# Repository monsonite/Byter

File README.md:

# Byter
A basic 8-bit, bit serial CPU in 74HCxx Logic.

## PART 1. Getting Started On The Basics.

Bit Serial Arithmetic is sufficiently obscure to most - you have to start with the basics.

When I started this journey during the first COVID lockdown - it took many iterations to get the basic hardware to work using the "Digital" simulator.

First you need a full adder, then extend it to a complete ALU.
 
You add your Accumulator and B shift registers and make a simple adder -subtractor.

You need the Carry Flipflop and the Carry injection and suppression logic.

Finally you need a a clock sequencer to make it all work correctly.

This repo - will takes you through the basics:

The following is NOT a full CPU, it is just an ALU testbed to ensure that the serial arithmetic process is working correctly.

### 1. INSTRUCTION DECODER

We start with the instruction Decoder.  U1 (74HC138) decodes the 3-bit instruction in IR6:4 into one of the 8 fundamental instruction groups:

LOAD

AND

OR

XOR

ADD

SUB

STORE

JUMP

The didode matrix and U2 (octal inverter 74HC540) converts these instructions into control signals that will control the ALU and carry logic.

The Instruction Decoder is entirely combinational logic, so could be reduced to basic gates or even coded into a ROM.

### 2. ALU

The ALU is entirely combinational logic made entirely from basic gates so could be coded into a ROM.

It has 12 inputs, and 5 outputs:

Ain   The bitstream from the Accumulator Shift Register

Bin   The bitstream from the B Shift Register

Cin   Any Carry generated from the previous bit-sum

InvA  Invert the A input for B-A subtraction operations

InvB  Invert the B input for A-B subtraction operations

Mode  Suppress Carry propagation for logical operations

SetC (T1)  Set the Carry on Timing Pulse T1

Sub   Asserted to indicate when a subtraction is performed

LDA (T0) Timing Pulse T0 initiates loading of the Accumulator

CLA  Clear Accumulator first, if a LOAD instruction is being performed

I0 Instruction input 0 - selects whether ALU output is the SUM function

I0 Instruction input  -  selects whether ALU output is the CARRY function

I1:I0   00    ZERO 

I1:I0   01    XOR

I1:I0   10    AND 

I1:I0   11    OR

OUTPUTS:

Fout  - The SUM Output of the ALU

Cout  - The CARRY output of the ALU

/CSET - Preset the Carry Flipflop

/CRES - Pre-clear the Carry Flipflop

/CLRACC - Clear the Accumulator

Details:

One quand 2-input XOR and three quad 2-input NANDs.  U10:U13.

U10, 11 and 12 make up the ALU, and U13 deals with the Carry suppress and injection logic.

U10 and U11 form a full adder with the means to invert either of the two inputs A and B.

U12 creates a 2 input multiplexer that chooses either the AND (CARRY) term or the XOR (SUM) term from the full adder.

U13 provides a means to inject a carry when it is needed and suppress the carry chain during logical operations.

### 3. The Clock Sequencer.

The clock sequencer is based around a 4-bit counter (74HC161) U8. When clocked, this counter will count from 0 to 15 and on the $0F count produces the RCO (Ripple Carry Out) signal. RCO is captured by one half of the dual flipflop U9 and is used to produce true and complementary timing pulses RUN and T0.

U7 (74HC00) is a clock gating circuit.  Two of the NAND gates are configured as a SR latch. RES goes low, and is used to reset the latch. This makes the output RST high and allows the clock signal CLK to pass to the counter U8. when RST goes high the counter is taken out of reset and begins to count upwards from 0 to 15.

RST is effectively a clock gating signal. When high it allows a burst of clocks to be sent to the various shift registers - thus synchronising their operations. The inverted form of RST is available from the output of the lower NAND gate. This can be used as a /CE or /SS (slave select) signal for enabling SPI peripherals.

Carry Flipflop.

The other half of dual flipflop U9 is the "Carry Flipflop".  If a positive carry is generated during a bit-sum, it will be stored in U9B and presented to the Carry In (Cin) input of the ALU on the next clock cycle. The set and reset inputs of the flipflop are used to set or clear the carry, as required by the instruction being performed. For example a subtraction requires the carry to be set first at the start of the calculation but bitwise boolean logical operations require the carry to be suppressed for the duration of the operation so that it does not propagate between the bits and corrupt the operation.

### 4. Registers.

I show 3 registers, The Accumulator AC, The B-Register and an Output Register. The output register just follows the Accumulator - but just latches its output result at the end of the machine cycle. All are 8-bits and they are co-ordinated by the timing pulses and the gated clock stream GCLK.

In the next part, I will show how other ICs can be used to replace U2, U10, 11, 12, 13 thus reducing the package count.  

The Instruction decoding logic can be simplified and the Carry Suppress logic moved to the Carry Flipflop, rather than using additional NAND gates.

The clock sequencer counter may be set to generate different numbers of pulses in the clock burst. These van be used to control the Accumulator to provide left and right shift operations and also a nybble swap operation between the upper 4-bits and the lower 4-bits.

## Part 2. Reducing package count - or getting more bang for your buck!

All combinational logic may ultimately be reduced to a ROM or other programmable logic such as PAL, GAL or FPGA.  These are all "blackbox" solutions, and not easy to follow as a newcomer to bit serial architechtures.

However, by carefully choosing devices that are more specialised, and contain more logic than basic 2-input gates, fairly large savings may be made in package count, and in some cases, these devices offer additional functionality, which previously would have required further packages.

I am initially going to focus on the Instruction Decoder and ALU. Between these sub-circuits, they use 6 packages, 1x 20 pin, 1x 16 pin and 4x 14-pin - plus an array of 15 diodes, which on a pcb would take up the same space as a pair of 14 pin DILs. 

We will keep U1, the 74HC138, as this is a very convenient way to perform the first stage of instruction decoding. We will eliminate the octal inverter and the diode matrix and its accompanying pull-up resistors.

We will minimise the rest of the decode logic finding a better overall solution for U12 and U13.

At the same time we will start to turn this manual adder/subtractor into a working CPU, allowing it to run stored programs from parallel memory.

This will require a Program Counter and additional circuitry, some of which will be absorbed into the enhanced ALU design.

A Better ALU Solution.

At this stage I would like to introduce the 74HC283 - it is a 4-bit parallel adder, with fast carry logic. Here you might say, but we only need a 1-bit full adder - a valid point. But the 74HC283 can provide an independent 1-bit full adder, and an independent 1-bit half-adder, which is exactly what we require for the Program Counter.

Here is the internal logic equivalent of the 74HC283. It contains a total of 50 inverters, buffers and multi-input gates.

For our purposes we are going to split it into 2 sections, a 1-bit half-adder and a 1-bit full adder.  

A half-adder adds 2 binary digits producing the outputs 00, 01, 10 or 11.  It cannot produce an output 100, which would propagate a carry into the next stage. 

We rely on this certainty, to allow us to split a 74HC283 into 2 entirely separate halves.

In the sketch above, the half-adder for the Program Counter is constrained to the left hand side of the IC, whilst the full-adder for the ALU is constrained to the right-hand side of the IC.  The half-adder can never propagate a carry beyond S2, so is effectively isolated from S3 and S4.

The remaining XOR gate is the means to invert the bitstream from the B-register when we are performing a A-B subtraction operation.

Output Multiplexer.

In our original prototype ALU, most of a 2-input quad NAND gate was being used as the output multiplexer, to select between the SUM and CARRY terms of the full-adder.

A simmilar 2-input multiplexer will be needed for the Program Counter, to select between incrementing the PC by 1, or jumping to a completely new address.

There are almost no independent dual 2-input multiplexers available, in a single package - so we will make our own from  quad tristate buffers, the 74HC126 and its sister chip the 74HC125. Here we rely on using the tristate enable signal to switch several signal sources onto the one data output. The 74HC126 has a logic 1 tristate enable and the 74HC125 has a logic 0 tristate enable. With a 125 and a 126 working together, we can have 4 independent 2 input multiplexers in just 2 14-pin packages.

But first we look at just the '126.

Here is a very specific use case, the ALU output multiplexer. Only the right hand of the IC is being used, the left hand side is available as another multiplexer.

We choose between using the ALU_SUM term or the ALU_CARRY term to provide our output function Fout.

Instruction control signals I0 and I1 are used to "steer" this logic selection.

If I0 is high we select the ALU_SUM, if I1 is high we select the ALU_CARRY.  If they are both low, both tristate buffers are off and a logic low is provided by the pull-down resistor.  If both I0 and I1 are high, thhe two diodes OR the outputs together providing a logical OR of the ALU operands.

If we need more than two independent multiplexers, we can combine a 125 and a 126 to make a 4 independent, 2 input multiplexers in a compact 2 chip solution.

Instruction Decoding, Subtraction and Carry Suppress Logic.

I have given this a revamp to remove the diode array and the octal inverter. It still uses the same 74HC138 for the initial instruction decode, but this is followed by three basic gate packages, a 74HC00 quad 2-input NAND, a 74HC86 quad 2-input XOR and a 74HC11 triple 3-input AND. The two inverters shown are actually XOR gates with one of their inputs tided high.

The ALU has also receiveed a makeover. Using the 74HC283 and 74HC126 it now has the additional functionality to accept a serial Program Counter.

BYTER now stands at 12 IC packages and is now ready to be converter from an anaemic calculator to a full system with ROM, RAM and I/O. Further IC reductions could be made by putting the entire INstruction Decoder, ALU, Program Counter logic and multiplexers into a small ROM.  About 4 or 5 ICs could be saved in this manner 

## PART 3. Adding Program Memory

A 16-bit Program Counter is needed to access the stored program in ROM. The Program Counter is just a pair of serial in, parallel output shift registers, coupled with a half adder and a multiplexer to allow jumps.

The unused left side of the ALU multiplexer is now used to provide a multiplexer for the Program Counter. The PC can either increment each machine cycle or by selecting the Jump instruction, it will be loaded with a number supplied from the B-Register.

To accommodate a 16-bit serial Program Counter, we must make changes to the Clock Sequencer. The PC requires 16 clock pulses to increment it, whilst the remainder of the 8-bit shift registers only require 8 clock pulses.

So we accept that GCLK - the gated clock is going to be a truncated version of PC-CLK, and we use output QD of the clock sequencer counter to allow only the first 8 clock pulses to reach GCLK, and the full 16 clocks to reach the PC.

## PART 4. Adding SRAM.

Byter can address 32K bytes of static RAM, using the common 62256 RAM device. Byter uses a modified Harvard architecture, which means that the ROM and RAM have seperate address and datapaths.

Whilst the ROM is addressed using a serial Program Counter, for the RAM we will take advantage of its parallel address bus, and that we can use the outputs of the ROM to directly supply the RAM with a 15-bit address - in parallel.

If bit 15 of the RAM is set to zero, the remaining 15 bits are taken to be an address in RAM, from which to load the Accumulator. For this to work, we need an Accumulator that can be loaded from an 8-bit parallel, tristate memory data bus.

Here we must substitute our simple 74HC164 Accumulator, for the 8-bit, universal, bidirectional tristate 74HC299.

The 74HC299 is an 8-bit shift register which may be loaded either from a serial bitstream, or from a Tristate 8-bit bus. Equally, it can shift data out serially or output a byte in parallel. It is this flexibility in operation which makes it so useful in this application.

The 74HC299 has two mode control inputs labelled S0 and S1, It also has two output enable inputs (/OE1, /OE2) for flexible connection to a tristate bus, and an asynchronous Master Reser (/MR) input.

The datasheet may be found here:  https://www.ti.com/lit/ds/symlink/cd74hc299.pdf

According to the datasheet, there are 4 modes of operation, controlled by the signals on S0 and S1.

S1:S0   00     Output data to bus (Store)

S1:S0   11     Input data from bus (Load)

S1:S0   01     Shift Right

S1:S0   10     Shift Left

## BYTER_03

Byter 03 takes us one step closer to a full functioning machine.  The 64K x 16-bit ROM is in place along with its 16-bit Program Counter. The RAM is connected to the Accumulator bus, but the Read/Write logic is still manual, as is the placement of an instruction.

The following must be implemented:

1.  Tie in the LOAD (1000) and STORE (1110) instructions to control the read and write to the RAM.

2.  Connect the ROM output IR7:IR4 to the instruction decoder inputs.

3.  Create a path between the ROM outputs 14:0 to the address lines

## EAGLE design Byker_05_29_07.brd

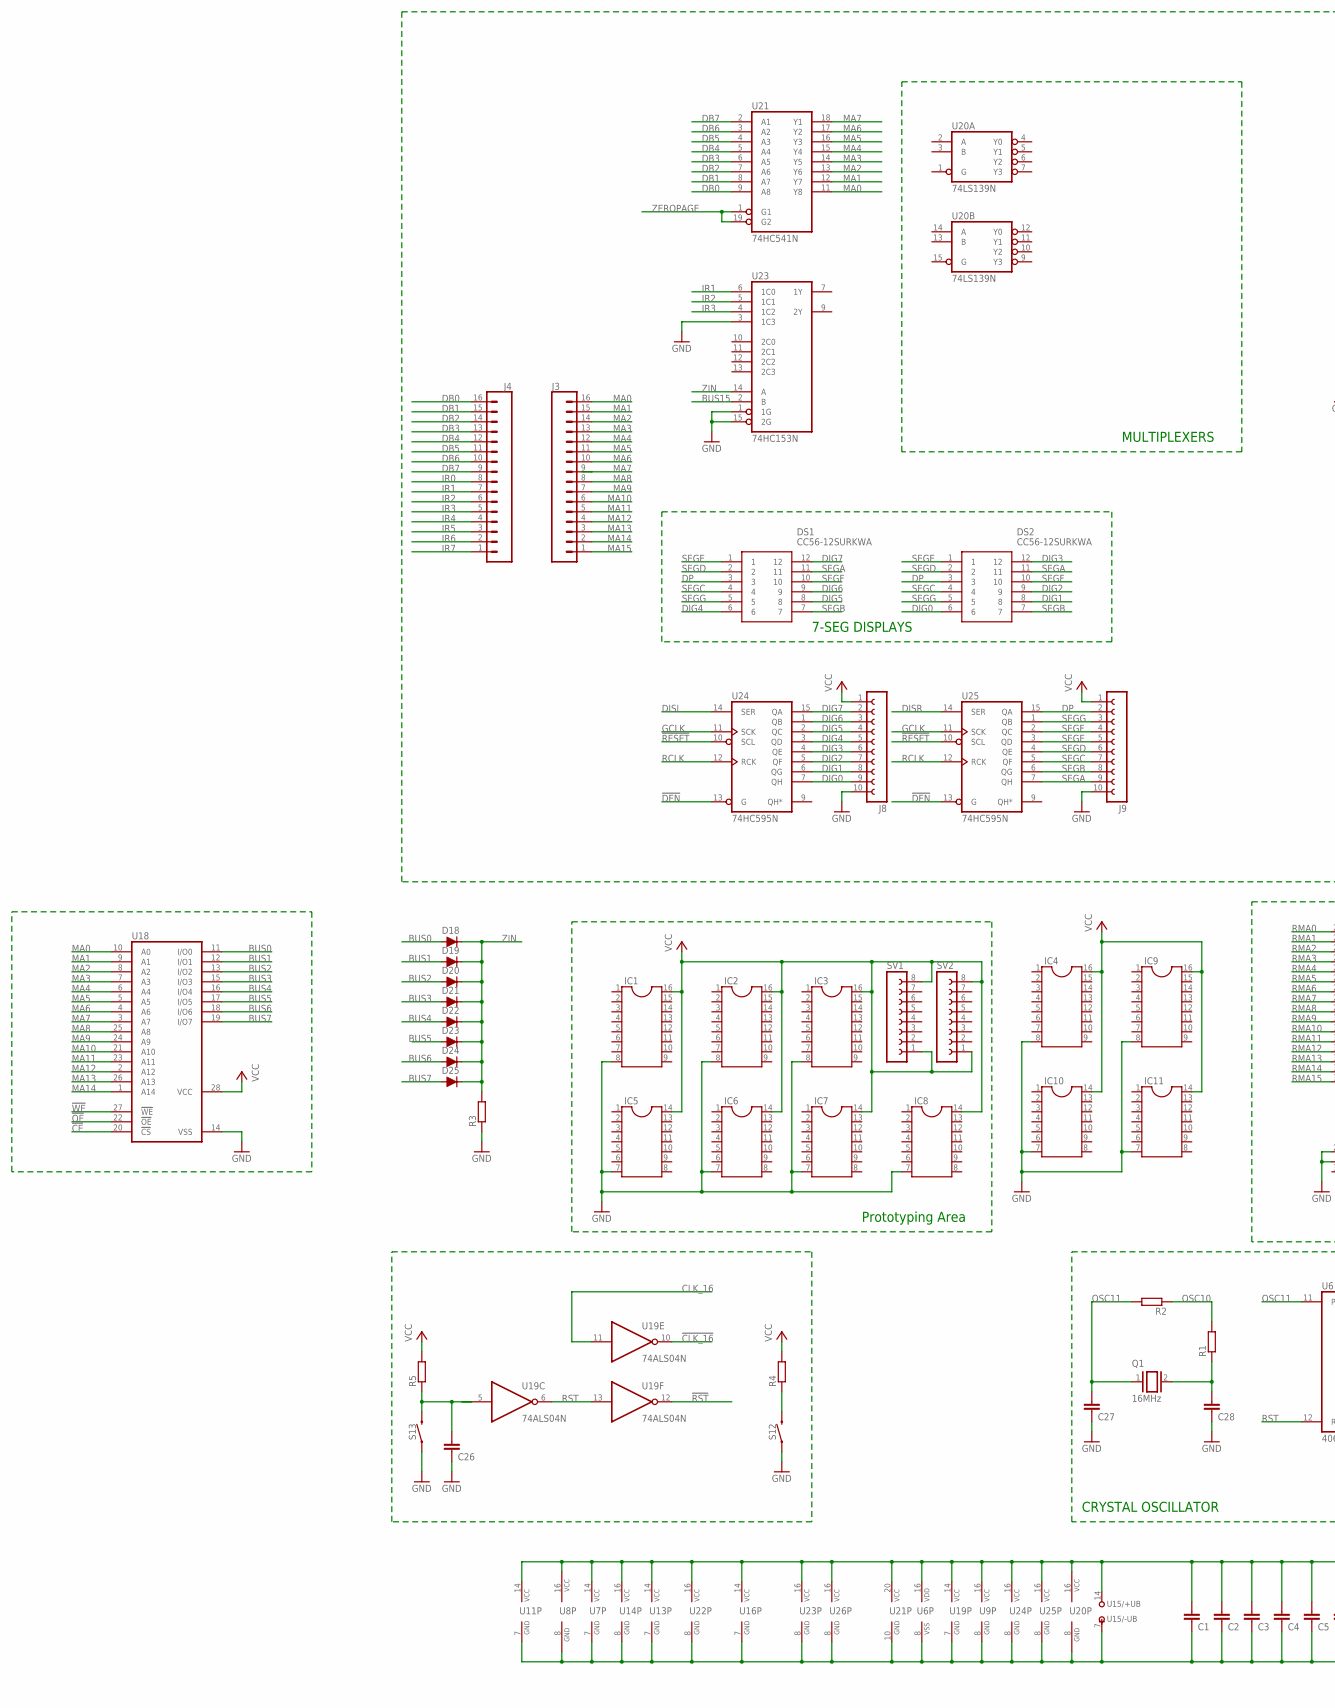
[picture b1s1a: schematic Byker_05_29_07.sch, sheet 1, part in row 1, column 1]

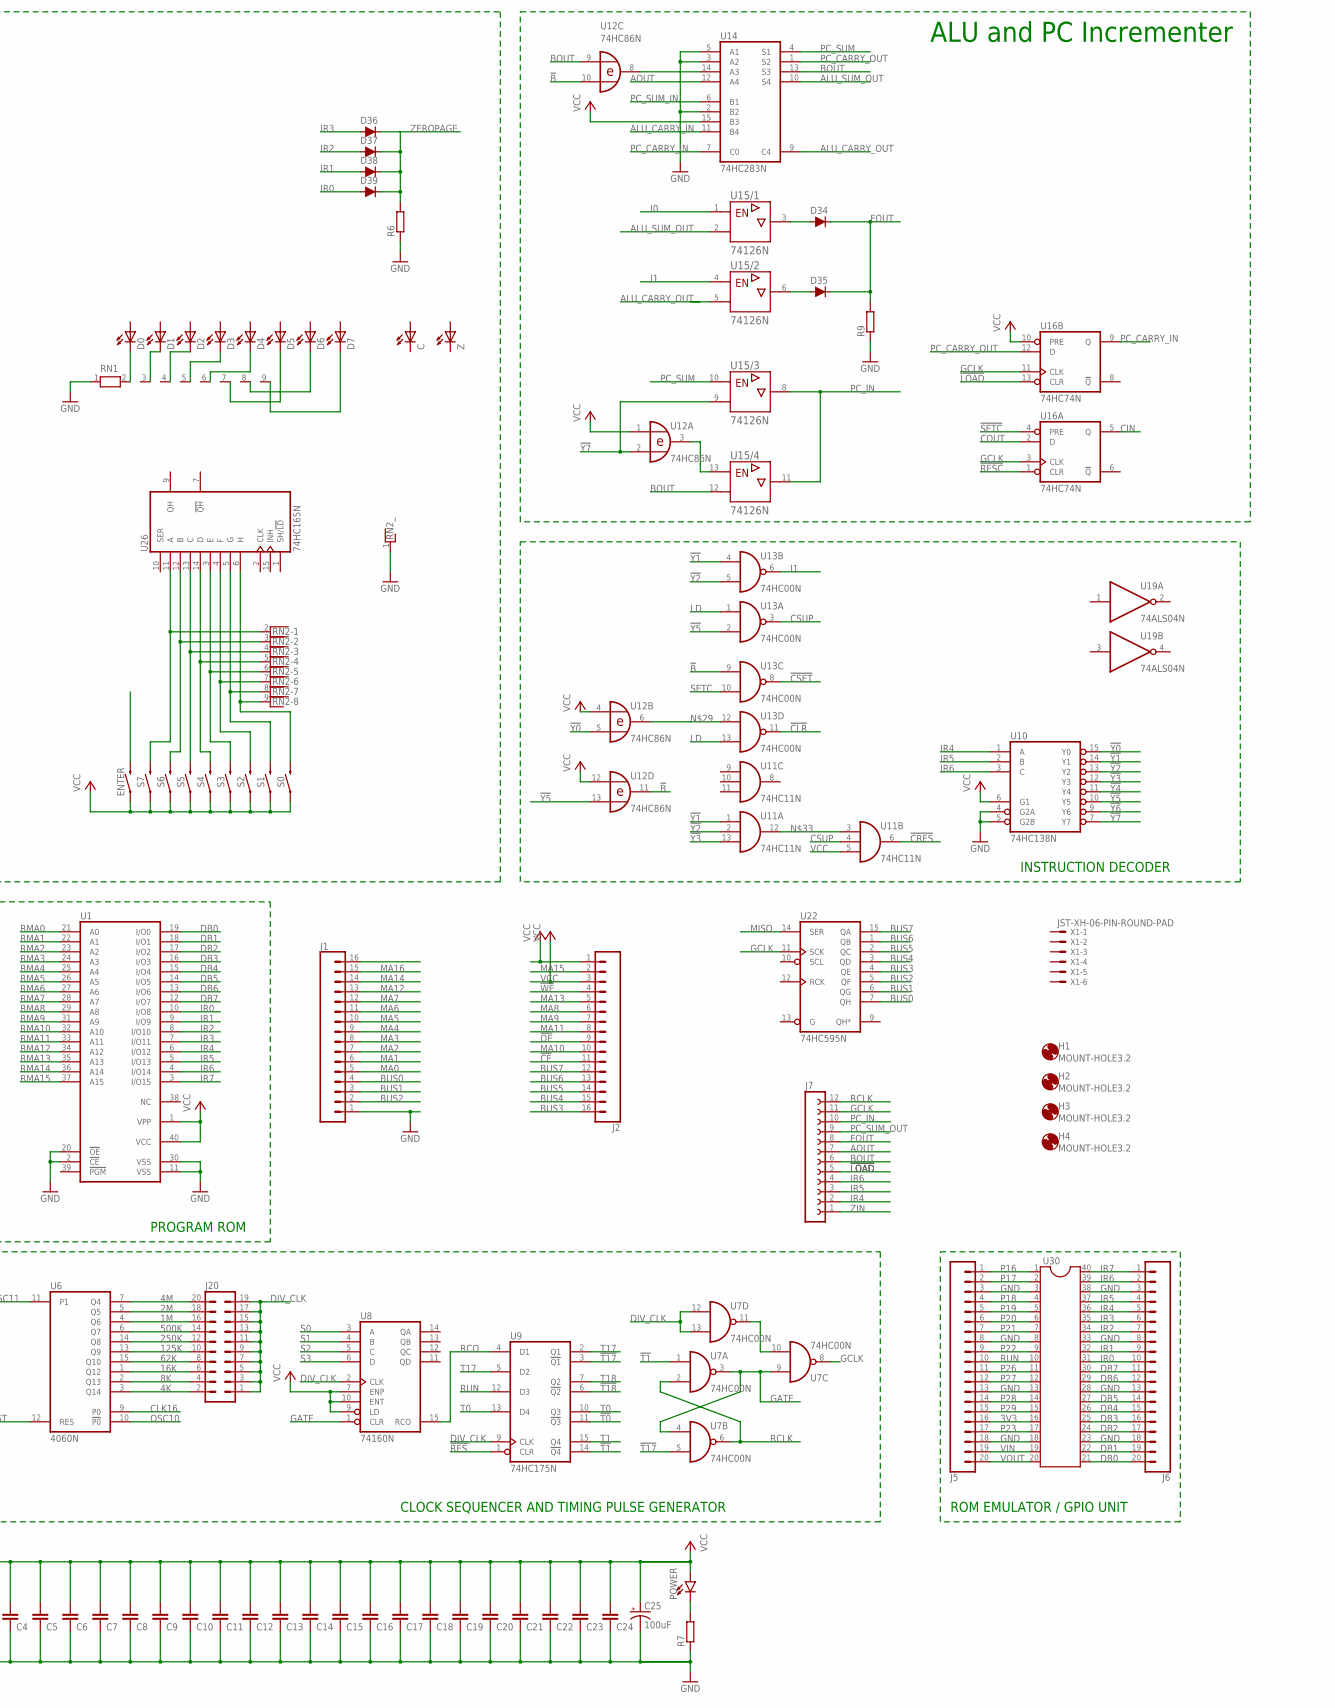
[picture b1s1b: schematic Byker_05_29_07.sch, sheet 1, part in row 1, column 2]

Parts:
C: LED3MM
C1, C2, C3, C4, C5, C6, C7, C8, C9, C10, C11, C12, C13, C14, C15, C16, C17, C18, C19, C20, C21, C22, C23, C24, C26, C27, C28: C-EU025-024X044; C025-024X044
C25: 100uF; CPOL-RADIAL-2.5MM-6.5MM
D0, D1, D2, D3, D4, D5, D6, D7: LED3MM
D18: 200mA/100V/1V; DIODE-1N4148-KIT
D19, D20, D21, D22, D23, D24, D25, D34, D35, D36, D37, D38, D39: 200mA/100V/1V; DIODE-1N4148
DS1, DS2: CC56-12SURKWA; DIPS1524W75P254L5030H810Q12N
ENTER: MOMENTARY-SWITCH-SPST-PTH-6.0MM; TACTILE_SWITCH_PTH_6.0MM
H1, H2, H3, H4: MOUNT-HOLE3.2; 3,2
IC1, IC2, IC3, IC4, IC9: DIL16
IC5, IC6, IC7, IC8, IC10, IC11: DIL14
J1, J2: CONN_161X16_NO_SILK; 1X16_NO_SILK
J3, J4: CONN_161X16_SM_SQ_NOSILK; 1X16_SM_SQ_NOSILK
J5, J6: CONN_20NOSILK; 1X20_NOSILK
J7: FE12-1; FE12
J8, J9: FE10-1; FE10
J20: MA10-2
POWER: LED3MM; LED_3MM
Q1: 16MHz; QS
R1, R2, R3, R4, R5, R6, R7, R9: R-EU_0204/5; 0204/5
RN1: RN08; RN-9
RN2: RNX8; RN-9
S0, S1, S2, S3, S4, S5, S6, S7, S12, S13: MOMENTARY-SWITCH-SPST-PTH-6.0MM; TACTILE_SWITCH_PTH_6.0MM
SV1, SV2: FE08-1; FE08
U1: 27C1024HG; DIL40
U6: 4060N; DIL16
U7, U13: 74HC00N; DIL14
U8: 74160N; DIL16
U9: 74HC175N; DIL16
U10: 74HC138N; DIL16
U11: 74HC11N; DIL14
U12: 74HC86N; DIL14
U14: 74HC283N; DIL16
U15: 74126N; DIL14
U16: 74HC74N; DIL14
U18: 62256P; DIL28-6
U19: 74ALS04N; DIL14
U20: 74LS139N; DIL16
U21: 74HC541N; DIL20
U22, U24, U25: 74HC595N; DIL16
U23: 74HC153N; DIL16
U26: 74HC165N; DIL16
U30: DIL40
X1: JST-XH-06-PIN-ROUND-PAD; JST-XH-06-PACKAGE-ROUND-PAD
Z: LED3MM

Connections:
1M: J20.16, U6.4 (Q6)
2M: J20.18, U6.5 (Q5)
3V3: J5.16, U30.16
4K: J20.2, U6.3 (Q14)
4M: J20.20, U6.7 (Q4)
8K: J20.4, U6.2 (Q13)
16K: J20.6, U6.1 (Q12)
62K: J20.8, U6.15 (Q10)
125K: J20.10, U6.13 (Q9)
250K: J20.12, U6.14 (Q8)
500K: J20.14, U6.6 (Q7)
!B: U12.10 (I1), U12.11 (O), U13.9 (I0)
!CE: J2.11, U18.20 (!CS)
!CLK_16: U19.10 (O)
!CLR: U13.11 (O); also elsewhere on the board
!CRES: U11.6 (O)
!CSET: U13.8 (O)
!DEN: U24.13 (G), U25.13 (G)
!LOAD: J7.5, U16.13 (CLR); also elsewhere on the board
!OE: J2.9, U18.22 (!OE)
!RES: U9.1 (CLR)
!RESC: U16.1 (CLR)
!RESET: U24.10 (SCL), U25.10 (SCL)
!RST: U19.12 (O)
!SETC: U16.4 (PRE)
!T0: U9.11 (!Q3)
!T1: U7.1 (I0), U9.14 (!Q4)
!T17: U7.5 (I1), U9.3 (!Q1)
!T18: U9.6 (!Q2)
!WE: J2.4, U18.27 (!WE); also elsewhere on the board
!Y0: U10.15 (Y0), U12.5 (I1)
!Y1: U10.14 (Y1), U11.1 (I0), U13.4 (I0)
!Y2: U10.13 (Y2), U11.2 (I1), U13.5 (I1)
!Y3: U10.12 (Y3), U11.13 (I2)
!Y4: U10.11 (Y4)
!Y5: U10.10 (Y5), U12.13 (I1), U13.2 (I1)
!Y6: U10.9 (Y6)
!Y7: U10.7 (Y7), U12.2 (I1), U15.9 (A)
ALU_CARRY_IN: U14.11 (B4)
ALU_CARRY_OUT: U14.9 (C4), U15.5 (A)
ALU_SUM_OUT: U14.10 (S4), U15.2 (A)
AOUT: J7.7, U14.12 (A4); also elsewhere on the board
BOUT: J7.6, U12.9 (I0), U14.13 (S3), U15.12 (A); also elsewhere on the board
BUS0: D18.A, J1.4, U18.11 (I/O0), U22.7 (QH); also elsewhere on the board
BUS1: D19.A, J1.3, U18.12 (I/O1), U22.6 (QG); also elsewhere on the board
BUS2: D20.A, J1.2, U18.13 (I/O2), U22.5 (QF); also elsewhere on the board
BUS3: D21.A, J2.16, U18.15 (I/O3), U22.4 (QE); also elsewhere on the board
BUS4: D22.A, J2.15, U18.16 (I/O4), U22.3 (QD); also elsewhere on the board
BUS5: D23.A, J2.14, U18.17 (I/O5), U22.2 (QC); also elsewhere on the board
BUS6: D24.A, J2.13, U18.18 (I/O6), U22.1 (QB); also elsewhere on the board
BUS7: D25.A, J2.12, U18.19 (I/O7), U22.15 (QA); also elsewhere on the board
BUS15: U23.2 (B)
CIN: U16.5 (Q)
CLK16: U6.9 (P0)
CLK_16: U19.11 (I)
COUT: U16.2 (D)
CSUP: U11.4 (I1), U13.3 (O)
DB0: J4.16, J6.20, U1.19 (I/O0), U21.9 (A8), U30.21; also elsewhere on the board
DB1: J4.15, J6.19, U1.18 (I/O1), U21.8 (A7), U30.22; also elsewhere on the board
DB2: J4.14, J6.17, U1.17 (I/O2), U21.7 (A6), U30.24; also elsewhere on the board
DB3: J4.13, J6.16, U1.16 (I/O3), U21.6 (A5), U30.25; also elsewhere on the board
DB4: J4.12, J6.15, U1.15 (I/O4), U21.5 (A4), U30.26; also elsewhere on the board
DB5: J4.11, J6.14, U1.14 (I/O5), U21.4 (A3), U30.27; also elsewhere on the board
DB6: J4.10, J6.12, U1.13 (I/O6), U21.3 (A2), U30.29; also elsewhere on the board
DB7: J4.9, J6.11, U1.12 (I/O7), U21.2 (A1), U30.30; also elsewhere on the board
DIG0: DS2.6, J8.9, U24.7 (QH)
DIG1: DS2.8, J8.8, U24.6 (QG)
DIG2: DS2.9, J8.7, U24.5 (QF)
DIG3: DS2.12, J8.6, U24.4 (QE)
DIG4: DS1.6, J8.5, U24.3 (QD)
DIG5: DS1.8, J8.4, U24.2 (QC)
DIG6: DS1.9, J8.3, U24.1 (QB)
DIG7: DS1.12, J8.2, U24.15 (QA)
DISL: U24.14 (SER)
DISR: U25.14 (SER)
DIV_CLK: J20.1, J20.3, J20.5, J20.7, J20.9, J20.11, J20.13, J20.15, J20.17, J20.19, U7.12 (I0), U7.13 (I1), U8.2 (CLK), U9.9 (CLK)
DP: DS1.3, DS2.3, J9.2, U25.15 (QA)
FOUT: D34.C, D35.C, J7.8, R9.2; also elsewhere on the board
GATE: U7.3 (O), U7.4 (I0), U7.9 (I0), U8.1 (CLR)
GCLK: J7.11, U7.8 (O), U16.3 (CLK), U16.11 (CLK), U22.11 (SCK), U24.11 (SCK), U25.11 (SCK); also elsewhere on the board
GND: C1.1, C2.1, C3.1, C4.1, C5.1, C6.1, C7.1, C8.1, C9.1, C10.1, C11.1, C12.1, C13.1, C14.1, C15.1, C16.1, C17.1, C18.1, C19.1, C20.1, C21.1, C22.1, C23.1, C24.1, C25.2 (-), C26.1, C27.1, C28.1, IC1.8, IC2.8, IC3.8, IC4.8, IC5.7, IC6.7, IC7.7, IC8.7, IC9.8, IC10.7, IC11.7, J1.1, J5.3, J5.8, J5.13, J5.18, J6.3, J6.8, J6.13, J6.18, J8.10, J9.10, R3.1, R6.1, R7.1, R9.1, RN1.1, RN2.1, S12.1, S13.1, U1.2 (!CE), U1.11 (VSS), U1.20 (!OE), U1.30 (VSS), U6.8 (VSS), U7.7 (GND), U8.8 (GND), U9.8 (GND), U10.4 (G2A), U10.5 (G2B), U10.8 (GND), U11.7 (GND), U12.7 (GND), U13.7 (GND), U14.2 (B2), U14.3 (A2), U14.5 (A1), U14.8 (GND), U15.7 (-UB), U16.7 (GND), U18.14 (VSS), U19.7 (GND), U20.8 (GND), U21.10 (GND), U22.8 (GND), U23.1 (1G), U23.3 (1C3), U23.8 (GND), U23.15 (2G), U24.8 (GND), U25.8 (GND), U26.8 (GND), U30.3, U30.8, U30.13, U30.18, U30.23, U30.28, U30.33, U30.38; also elsewhere on the board
I0: U15.1 (G)
I1: U13.6 (O), U15.4 (G)
IR0: D39.A, J4.8, J6.10, U1.10 (I/O8), U30.31; also elsewhere on the board
IR1: D38.A, J4.7, J6.9, U1.9 (I/O9), U23.6 (1C0), U30.32; also elsewhere on the board
IR2: D37.A, J4.6, J6.7, U1.8 (I/O10), U23.5 (1C1), U30.34; also elsewhere on the board
IR3: D36.A, J4.5, J6.6, U1.7 (I/O11), U23.4 (1C2), U30.35; also elsewhere on the board
IR4: J4.4, J6.5, J7.2, U1.6 (I/O12), U10.1 (A), U30.36; also elsewhere on the board
IR5: J4.3, J6.4, J7.3, U1.5 (I/O13), U10.2 (B), U30.37; also elsewhere on the board
IR6: J4.2, J6.2, J7.4, U1.4 (I/O14), U10.3 (C), U30.39; also elsewhere on the board
IR7: J4.1, J6.1, U1.3 (I/O15), U30.40; also elsewhere on the board
LD: U13.1 (I0), U13.13 (I1)
MA0: J1.5, J3.16, U18.10 (A0), U21.11 (Y8)
MA1: J1.6, J3.15, U18.9 (A1), U21.12 (Y7)
MA2: J1.7, J3.14, U18.8 (A2), U21.13 (Y6)
MA3: J1.8, J3.13, U18.7 (A3), U21.14 (Y5)
MA4: J1.9, J3.12, U18.6 (A4), U21.15 (Y4)
MA5: J1.10, J3.11, U18.5 (A5), U21.16 (Y3)
MA6: J1.11, J3.10, U18.4 (A6), U21.17 (Y2)
MA7: J1.12, J3.9, U18.3 (A7), U21.18 (Y1)
MA8: J2.6, J3.8, U18.25 (A8)
MA9: J2.7, J3.7, U18.24 (A9)
MA10: J2.10, J3.6, U18.21 (A10)
MA11: J2.8, J3.5, U18.23 (A11)
MA12: J1.13, J3.4, U18.2 (A12)
MA13: J2.5, J3.3, U18.26 (A13)
MA14: J1.14, J3.2, U18.1 (A14)
MA15: J2.2, J3.1
MA16: J1.15
MISO: U22.14 (SER)
unnamed: D0.K (C), RN1.2
unnamed: D1.K (C), RN1.3
unnamed: U7.10 (I1), U7.11 (O)
unnamed: D2.K (C), RN1.4
unnamed: D34.A, U15.3 (Y)
unnamed: R4.1, S12.3 (2)
unnamed: C26.2, R5.1, S13.3 (2), U19.5 (I)
unnamed: POWER.K (C), R7.2
unnamed: U12.8 (O), U14.14 (A3)
unnamed: D35.A, U15.6 (Y)
unnamed: D3.K (C), RN1.5
unnamed: D4.K (C), RN1.6
unnamed: D5.K (C), RN1.7
unnamed: D6.K (C), RN1.8
unnamed: D7.K (C), RN1.9
unnamed: U11.3 (I0), U11.12 (O)
unnamed: RN2.2, S7.3 (2), U26.11 (A)
unnamed: RN2.3, S6.3 (2), U26.12 (B)
unnamed: RN2.4, S5.3 (2), U26.13 (C)
unnamed: RN2.5, S4.3 (2), U26.14 (D)
unnamed: RN2.6, S3.3 (2), U26.3 (E)
unnamed: RN2.7, S2.3 (2), U26.4 (F)
unnamed: U12.3 (O), U15.13 (G)
unnamed: RN2.8, S1.3 (2), U26.5 (G)
unnamed: RN2.9, S0.3 (2), U26.6 (H)
unnamed: C28.2, Q1.2, R1.1
OSC10: R1.2, R2.1, U6.10 (!P0)
OSC11: C27.2, Q1.1, R2.2, U6.11 (P1)
P16: J5.1, U30.1
P17: J5.2, U30.2
P18: J5.4, U30.4
P19: J5.5, U30.5
P20: J5.6, U30.6
P21: J5.7, U30.7
P22: J5.9, U30.9
P23: J5.17, U30.17
P26: J5.11, U30.11
P27: J5.12, U30.12
P28: J5.14, U30.14
P29: J5.15, U30.15
PC_CARRY_IN: U14.7 (C0), U16.9 (Q)
PC_CARRY_OUT: U14.1 (S2), U16.12 (D)
PC_IN: J7.10, U15.8 (Y), U15.11 (Y); also elsewhere on the board
PC_SUM: U14.4 (S1), U15.10 (G)
PC_SUM_IN: U14.6 (B1)
PC_SUM_OUT: J7.9; also elsewhere on the board
RCLK: J7.12, U7.2 (I1), U7.6 (O), U24.12 (RCK), U25.12 (RCK); also elsewhere on the board
RCO: U8.15 (RCO), U9.4 (D1)
RMA0: U1.21 (A0); also elsewhere on the board
RMA1: U1.22 (A1); also elsewhere on the board
RMA2: U1.23 (A2); also elsewhere on the board
RMA3: U1.24 (A3); also elsewhere on the board
RMA4: U1.25 (A4); also elsewhere on the board
RMA5: U1.26 (A5); also elsewhere on the board
RMA6: U1.27 (A6); also elsewhere on the board
RMA7: U1.28 (A7); also elsewhere on the board
RMA8: U1.29 (A8); also elsewhere on the board
RMA9: U1.31 (A9); also elsewhere on the board
RMA10: U1.32 (A10); also elsewhere on the board
RMA11: U1.33 (A11); also elsewhere on the board
RMA12: U1.34 (A12); also elsewhere on the board
RMA13: U1.35 (A13); also elsewhere on the board
RMA14: U1.36 (A14); also elsewhere on the board
RMA15: U1.37 (A15); also elsewhere on the board
RST: U6.12 (RES), U19.6 (O), U19.13 (I)
RUN: J5.10, U9.12 (D3), U30.10
S0: U8.3 (A)
S1: U8.4 (B)
S2: U8.5 (C)
S3: U8.6 (D)
SEGA: DS1.11, DS2.11, J9.9, U25.7 (QH)
SEGB: DS1.7, DS2.7, J9.8, U25.6 (QG)
SEGC: DS1.4, DS2.4, J9.7, U25.5 (QF)
SEGD: DS1.2, DS2.2, J9.6, U25.4 (QE)
SEGE: DS1.1, DS2.1, J9.5, U25.3 (QD)
SEGF: DS1.10, DS2.10, J9.4, U25.2 (QC)
SEGG: DS1.5, DS2.5, J9.3, U25.1 (QB)
SETC: U13.10 (I1)
T0: U9.10 (Q3), U9.13 (D4)
T1: U9.15 (Q4)
T17: U9.2 (Q1), U9.5 (D2)
T18: U9.7 (Q2)
VCC: C1.2, C2.2, C3.2, C4.2, C5.2, C6.2, C7.2, C8.2, C9.2, C10.2, C11.2, C12.2, C13.2, C14.2, C15.2, C16.2, C17.2, C18.2, C19.2, C20.2, C21.2, C22.2, C23.2, C24.2, C25.1 (+), ENTER.1, IC1.16, IC2.16, IC3.16, IC4.16, IC5.14, IC6.14, IC7.14, IC8.14, IC9.16, IC10.14, IC11.14, J2.1, J2.3, J8.1, J9.1, POWER.A, R4.2, R5.2, S0.1, S1.1, S2.1, S3.1, S4.1, S5.1, S6.1, S7.1, SV1.1, SV1.8, SV2.1, SV2.8, U1.1 (VPP), U1.40 (VCC), U6.16 (VDD), U7.14 (VCC), U8.7 (ENP), U8.9 (LD), U8.10 (ENT), U8.16 (VCC), U9.16 (VCC), U10.6 (G1), U10.16 (VCC), U11.5 (I2), U11.14 (VCC), U12.1 (I0), U12.4 (I0), U12.12 (I0), U12.14 (VCC), U13.14 (VCC), U14.15 (B3), U14.16 (VCC), U15.14 (+UB), U16.10 (PRE), U16.14 (VCC), U18.28 (VCC), U19.14 (VCC), U20.16 (VCC), U21.20 (VCC), U22.16 (VCC), U23.16 (VCC), U24.16 (VCC), U25.16 (VCC), U26.16 (VCC); also elsewhere on the board
VIN: J5.19, U30.19
VOUT: J5.20, U30.20
ZEROPAGE: D36.C, D37.C, D38.C, D39.C, R6.2, U21.1 (G1), U21.19 (G2)
ZIN: D18.C, D19.C, D20.C, D21.C, D22.C, D23.C, D24.C, D25.C, J7.1, R3.2, U23.14 (A)

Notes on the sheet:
ALU and PC Incrementer
CLOCK SEQUENCER AND TIMING PULSE GENERATOR
CRYSTAL OSCILLATOR
MULTIPLEXERS
INSTRUCTION DECODER
ROM EMULATOR / GPIO UNIT
PROGRAM ROM
7-SEG DISPLAYS
Prototyping Area

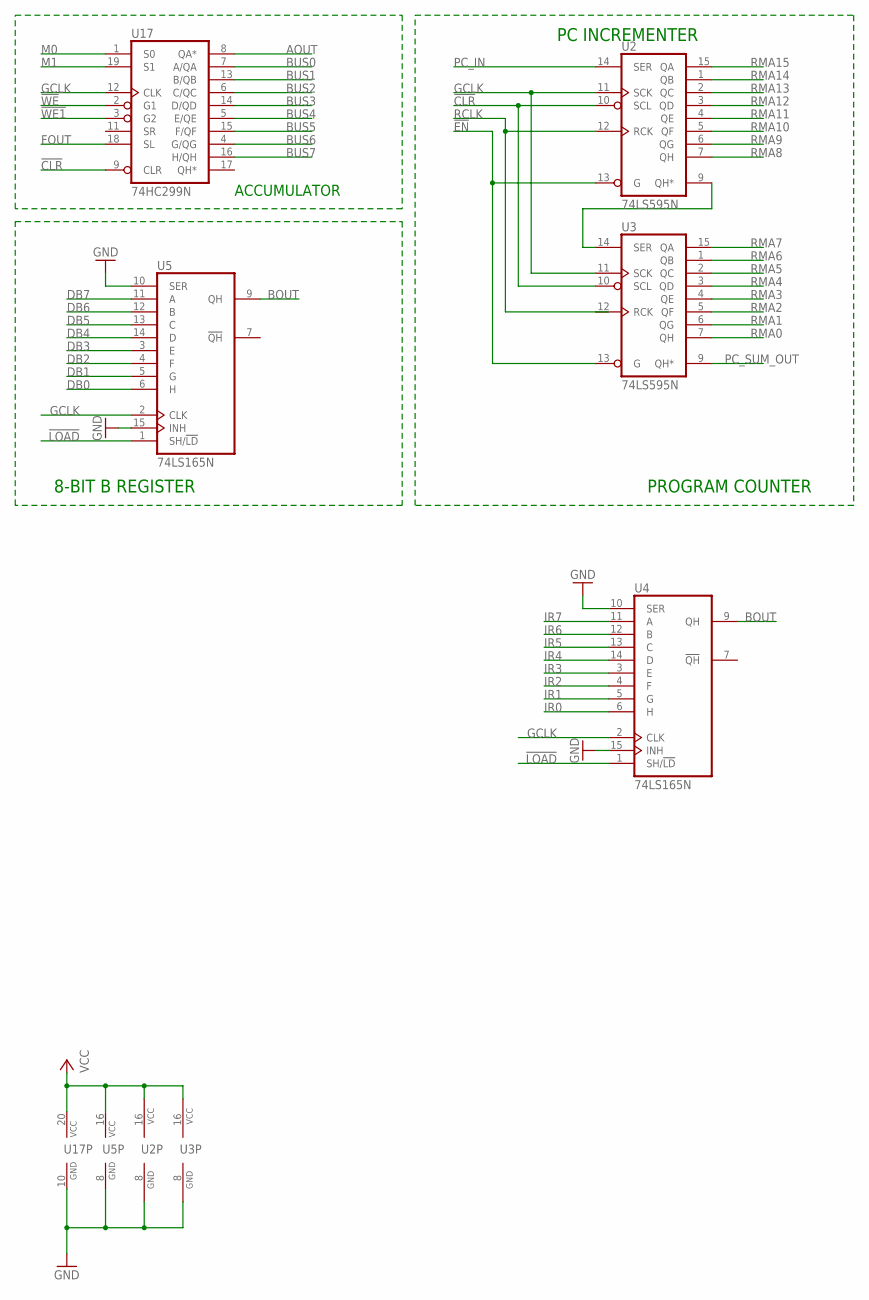
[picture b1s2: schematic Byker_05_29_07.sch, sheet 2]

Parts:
U2, U3: 74LS595N; DIL16
U4, U5: 74LS165N; DIL16
U17: 74HC299N; DIL20

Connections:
!CLR: U2.10 (SCL), U3.10 (SCL), U17.9 (CLR); also elsewhere on the board
!EN: U2.13 (G), U3.13 (G)
!LOAD: U4.1 (SH/!LD), U5.1 (SH/!LD); also elsewhere on the board
!WE: U17.2 (G1); also elsewhere on the board
!WE1: U17.3 (G2)
AOUT: U17.8 (QA*); also elsewhere on the board
BOUT: U4.9 (QH), U5.9 (QH); also elsewhere on the board
BUS0: U17.7 (A/QA); also elsewhere on the board
BUS1: U17.13 (B/QB); also elsewhere on the board
BUS2: U17.6 (C/QC); also elsewhere on the board
BUS3: U17.14 (D/QD); also elsewhere on the board
BUS4: U17.5 (E/QE); also elsewhere on the board
BUS5: U17.15 (F/QF); also elsewhere on the board
BUS6: U17.4 (G/QG); also elsewhere on the board
BUS7: U17.16 (H/QH); also elsewhere on the board
DB0: U5.6 (H); also elsewhere on the board
DB1: U5.5 (G); also elsewhere on the board
DB2: U5.4 (F); also elsewhere on the board
DB3: U5.3 (E); also elsewhere on the board
DB4: U5.14 (D); also elsewhere on the board
DB5: U5.13 (C); also elsewhere on the board
DB6: U5.12 (B); also elsewhere on the board
DB7: U5.11 (A); also elsewhere on the board
FOUT: U17.18 (SL); also elsewhere on the board
GCLK: U2.11 (SCK), U3.11 (SCK), U4.2 (CLK), U5.2 (CLK), U17.12 (CLK); also elsewhere on the board
GND: U2.8 (GND), U3.8 (GND), U4.8 (GND), U4.10 (SER), U4.15 (INH), U5.8 (GND), U5.10 (SER), U5.15 (INH), U17.10 (GND); also elsewhere on the board
IR0: U4.6 (H); also elsewhere on the board
IR1: U4.5 (G); also elsewhere on the board
IR2: U4.4 (F); also elsewhere on the board
IR3: U4.3 (E); also elsewhere on the board
IR4: U4.14 (D); also elsewhere on the board
IR5: U4.13 (C); also elsewhere on the board
IR6: U4.12 (B); also elsewhere on the board
IR7: U4.11 (A); also elsewhere on the board
M0: U17.1 (S0)
M1: U17.19 (S1)
unnamed: U2.9 (QH*), U3.14 (SER)
PC_IN: U2.14 (SER); also elsewhere on the board
PC_SUM_OUT: U3.9 (QH*); also elsewhere on the board
RCLK: U2.12 (RCK), U3.12 (RCK); also elsewhere on the board
RMA0: U3.7 (QH); also elsewhere on the board
RMA1: U3.6 (QG); also elsewhere on the board
RMA2: U3.5 (QF); also elsewhere on the board
RMA3: U3.4 (QE); also elsewhere on the board
RMA4: U3.3 (QD); also elsewhere on the board
RMA5: U3.2 (QC); also elsewhere on the board
RMA6: U3.1 (QB); also elsewhere on the board
RMA7: U3.15 (QA); also elsewhere on the board
RMA8: U2.7 (QH); also elsewhere on the board
RMA9: U2.6 (QG); also elsewhere on the board
RMA10: U2.5 (QF); also elsewhere on the board
RMA11: U2.4 (QE); also elsewhere on the board
RMA12: U2.3 (QD); also elsewhere on the board
RMA13: U2.2 (QC); also elsewhere on the board
RMA14: U2.1 (QB); also elsewhere on the board
RMA15: U2.15 (QA); also elsewhere on the board
VCC: U2.16 (VCC), U3.16 (VCC), U4.16 (VCC), U5.16 (VCC), U17.20 (VCC); also elsewhere on the board

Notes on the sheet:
ACCUMULATOR
8-BIT B REGISTER
PC INCREMENTER
PROGRAM COUNTER

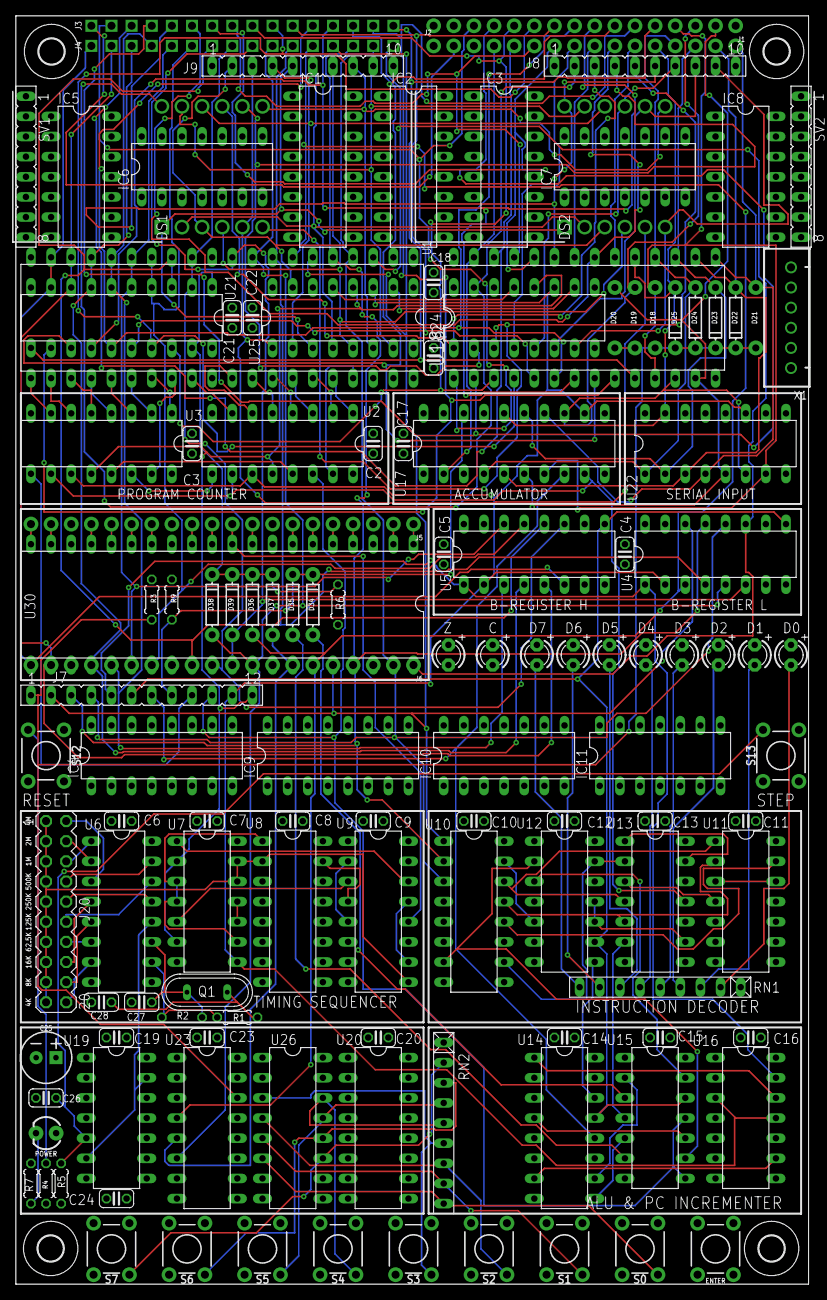
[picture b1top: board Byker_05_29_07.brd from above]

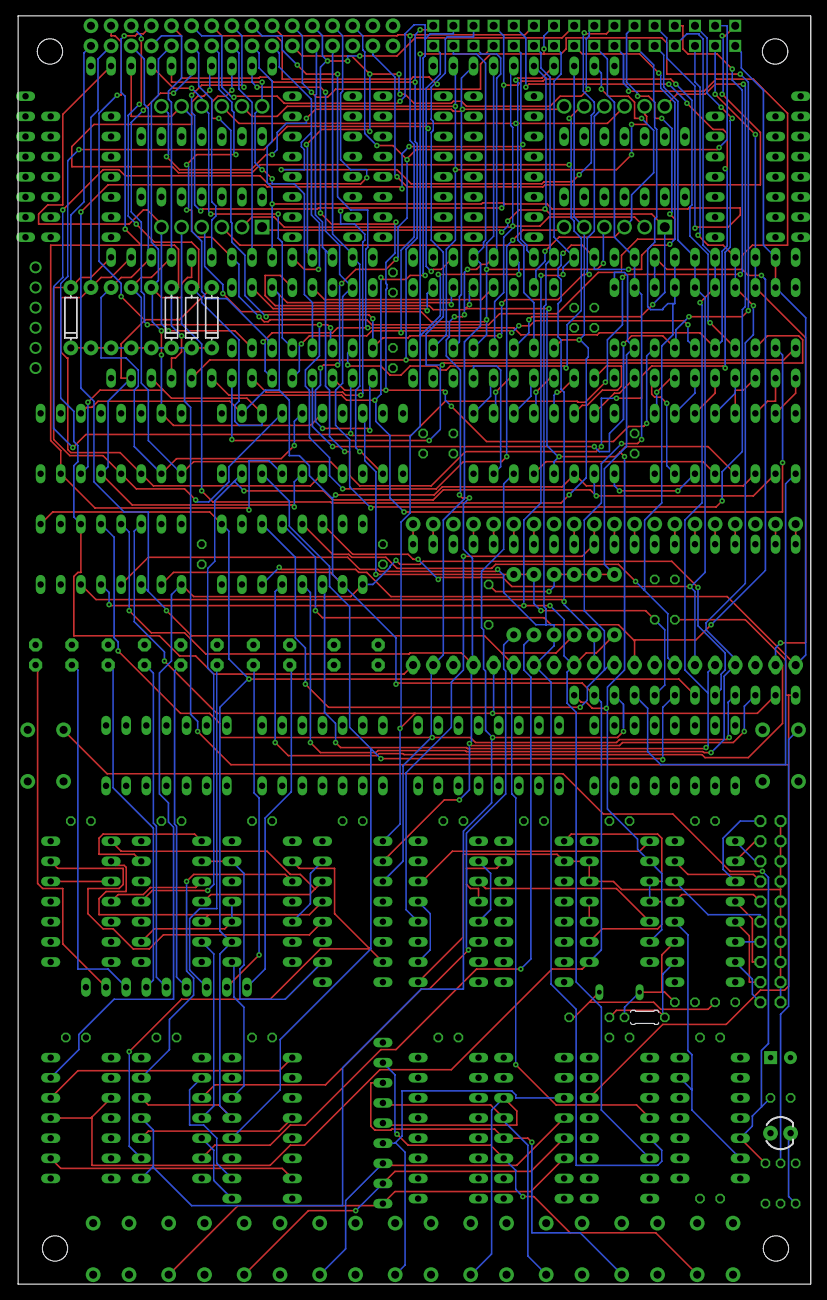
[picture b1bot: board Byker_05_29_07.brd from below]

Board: 4 copper layers, 100.0 x 160.0 mm, 132 parts (5 on the bottom side), 169 nets.

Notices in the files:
parts and their libraries:
SparkFun-DiscreteSemi: Licensing: Creative Commons ShareAlike 4.0 International - https://creativecommons.org/licenses/by-sa/4.0
